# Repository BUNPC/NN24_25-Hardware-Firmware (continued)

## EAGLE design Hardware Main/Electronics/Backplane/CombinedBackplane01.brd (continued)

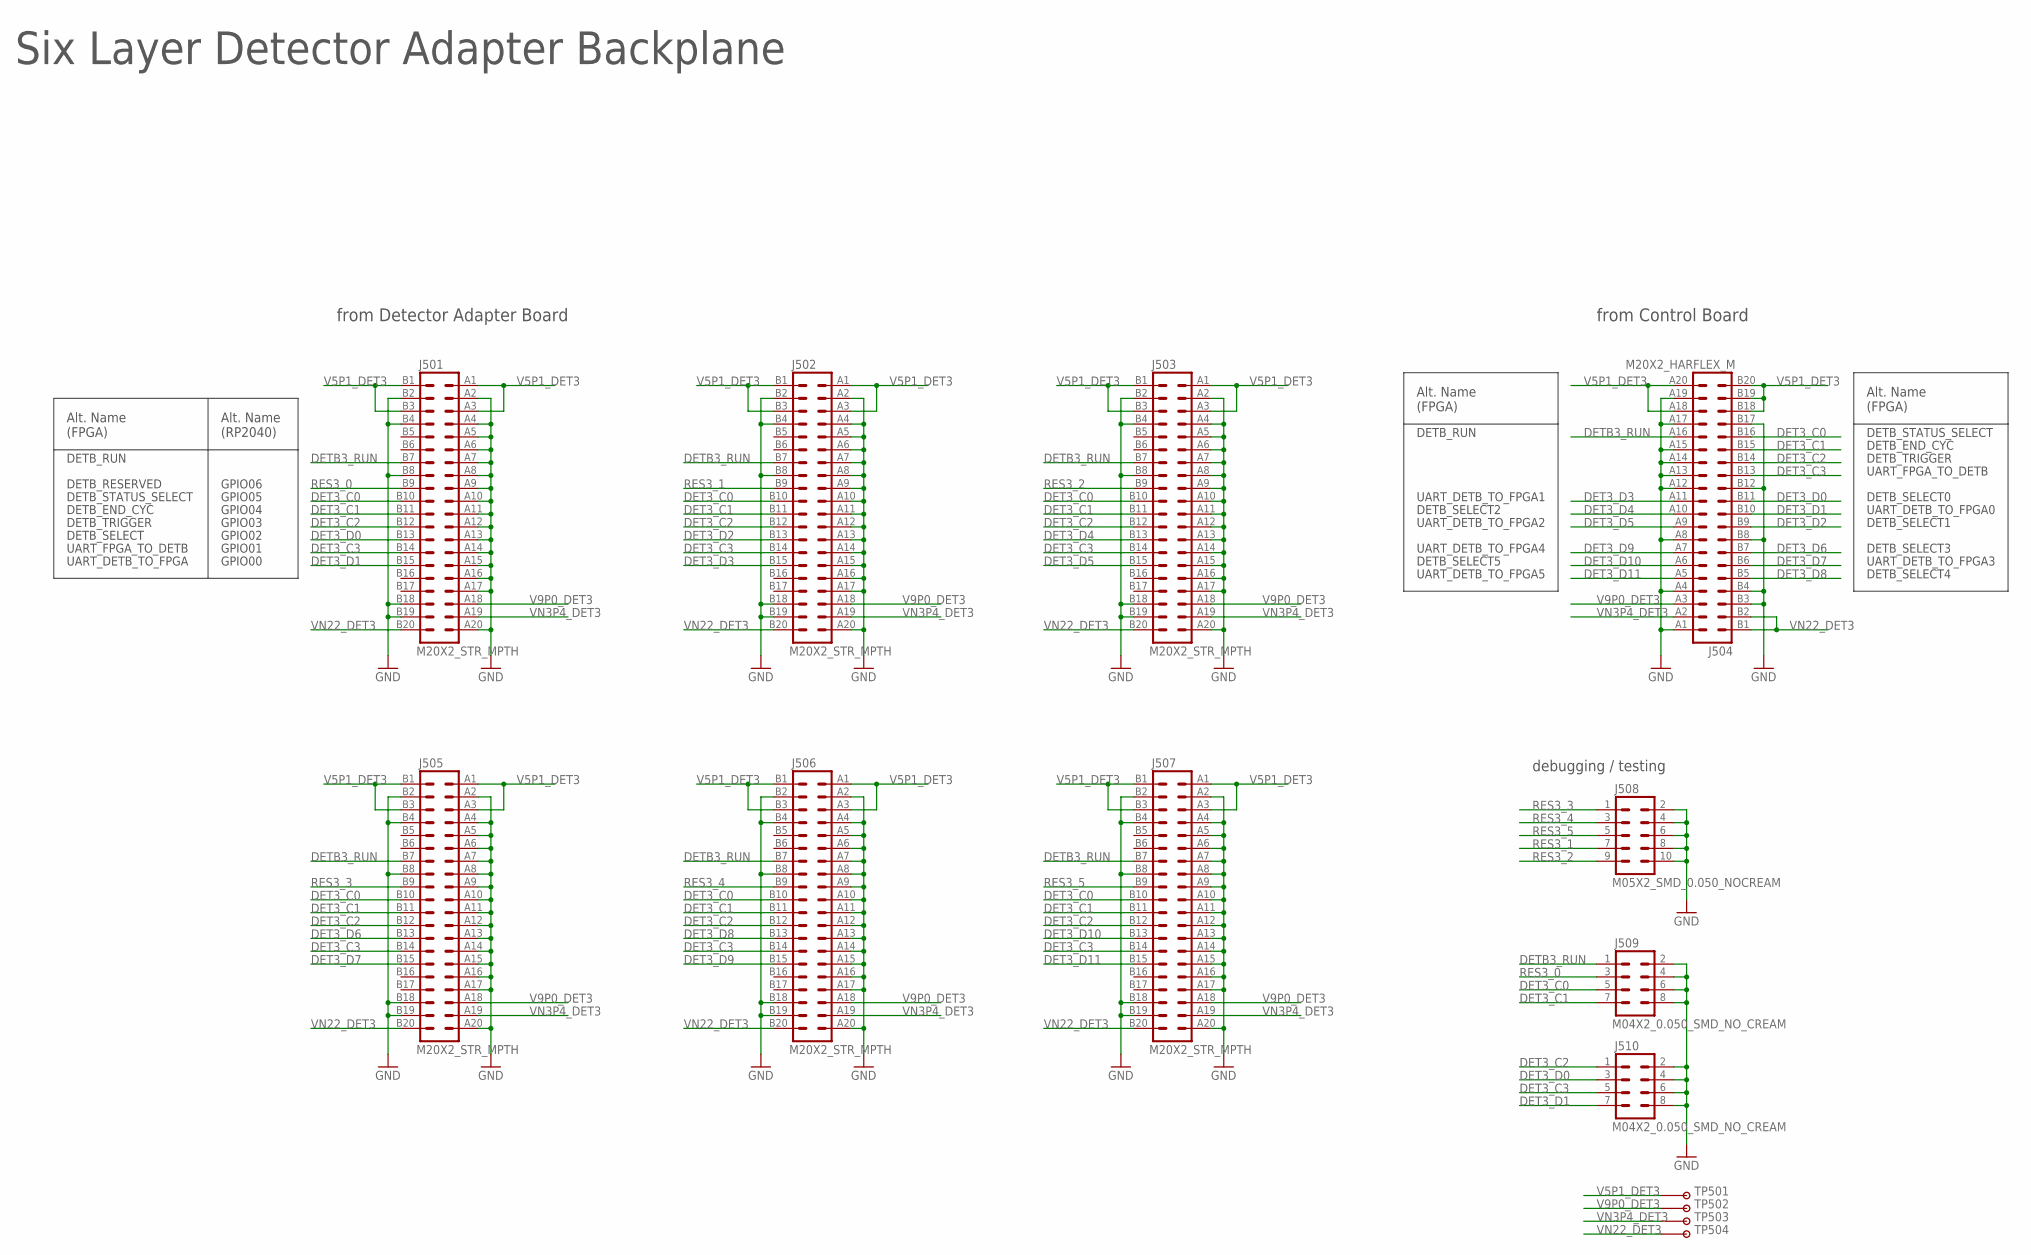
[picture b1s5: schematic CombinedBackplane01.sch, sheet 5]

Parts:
J501, J502, J503, J505, J506, J507: M20X2_STR_MPTH; M20X2_HARFLEX_F_STR_MPTH
J504: M20X2_HARFLEX_M
J508: M05X2_SMD_0.050_NOCREAM; M05X2_0.050_SMD_NO_CREAM
J509, J510: M04X2_0.050_SMD_NO_CREAM
TP501, TP502, TP503, TP504: TESTPOINT_ROUND; TESTPAD_ROUND

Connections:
DET3_C0: J501.B10 (19), J502.B10 (19), J503.B10 (19), J504.B16 (31), J505.B10 (19), J506.B10 (19), J507.B10 (19), J509.5
DET3_C1: J501.B11 (21), J502.B11 (21), J503.B11 (21), J504.B15 (29), J505.B11 (21), J506.B11 (21), J507.B11 (21), J509.7
DET3_C2: J501.B12 (23), J502.B12 (23), J503.B12 (23), J504.B14 (27), J505.B12 (23), J506.B12 (23), J507.B12 (23), J510.1
DET3_C3: J501.B14 (27), J502.B14 (27), J503.B14 (27), J504.B13 (25), J505.B14 (27), J506.B14 (27), J507.B14 (27), J510.5
DET3_D0: J501.B13 (25), J504.B11 (21), J510.3
DET3_D1: J501.B15 (29), J504.B10 (19), J510.7
DET3_D2: J502.B13 (25), J504.B9 (17)
DET3_D3: J502.B15 (29), J504.A11 (22)
DET3_D4: J503.B13 (25), J504.A10 (20)
DET3_D5: J503.B15 (29), J504.A9 (18)
DET3_D6: J504.B7 (13), J505.B13 (25)
DET3_D7: J504.B6 (11), J505.B15 (29)
DET3_D8: J504.B5 (9), J506.B13 (25)
DET3_D9: J504.A7 (14), J506.B15 (29)
DET3_D10: J504.A6 (12), J507.B13 (25)
DET3_D11: J504.A5 (10), J507.B15 (29)
DETB3_RUN: J501.B7 (13), J502.B7 (13), J503.B7 (13), J504.A16 (32), J505.B7 (13), J506.B7 (13), J507.B7 (13), J509.1
GND: J501.A2 (4), J501.A4 (8), J501.A5 (10), J501.A6 (12), J501.A7 (14), J501.A8 (16), J501.A9 (18), J501.A10 (20), J501.A11 (22), J501.A12 (24), J501.A13 (26), J501.A14 (28), J501.A15 (30), J501.A16 (32), J501.A17 (34), J501.A20 (40), J501.B2 (3), J501.B4 (7), J501.B8 (15), J501.B18 (35), J501.B19 (37), J502.A2 (4), J502.A4 (8), J502.A5 (10), J502.A6 (12), J502.A7 (14), J502.A8 (16), J502.A9 (18), J502.A10 (20), J502.A11 (22), J502.A12 (24), J502.A13 (26), J502.A14 (28), J502.A15 (30), J502.A16 (32), J502.A17 (34), J502.A20 (40), J502.B2 (3), J502.B4 (7), J502.B8 (15), J502.B18 (35), J502.B19 (37), J503.A2 (4), J503.A4 (8), J503.A5 (10), J503.A6 (12), J503.A7 (14), J503.A8 (16), J503.A9 (18), J503.A10 (20), J503.A11 (22), J503.A12 (24), J503.A13 (26), J503.A14 (28), J503.A15 (30), J503.A16 (32), J503.A17 (34), J503.A20 (40), J503.B2 (3), J503.B4 (7), J503.B8 (15), J503.B18 (35), J503.B19 (37), J504.A1 (2), J504.A4 (8), J504.A8 (16), J504.A12 (24), J504.A13 (26), J504.A14 (28), J504.A15 (30), J504.A17 (34), J504.A19 (38), J504.B3 (5), J504.B4 (7), J504.B8 (15), J504.B12 (23), J504.B17 (33), J505.A2 (4), J505.A4 (8), J505.A5 (10), J505.A6 (12), J505.A7 (14), J505.A8 (16), J505.A9 (18), J505.A10 (20), J505.A11 (22), J505.A12 (24), J505.A13 (26), J505.A14 (28), J505.A15 (30), J505.A16 (32), J505.A17 (34), J505.A20 (40), J505.B2 (3), J505.B4 (7), J505.B8 (15), J505.B18 (35), J505.B19 (37), J506.A2 (4), J506.A4 (8), J506.A5 (10), J506.A6 (12), J506.A7 (14), J506.A8 (16), J506.A9 (18), J506.A10 (20), J506.A11 (22), J506.A12 (24), J506.A13 (26), J506.A14 (28), J506.A15 (30), J506.A16 (32), J506.A17 (34), J506.A20 (40), J506.B2 (3), J506.B4 (7), J506.B8 (15), J506.B18 (35), J506.B19 (37), J507.A2 (4), J507.A4 (8), J507.A5 (10), J507.A6 (12), J507.A7 (14), J507.A8 (16), J507.A9 (18), J507.A10 (20), J507.A11 (22), J507.A12 (24), J507.A13 (26), J507.A14 (28), J507.A15 (30), J507.A16 (32), J507.A17 (34), J507.A20 (40), J507.B2 (3), J507.B4 (7), J507.B8 (15), J507.B18 (35), J507.B19 (37), J508.2, J508.4, J508.6, J508.8, J508.10, J509.2, J509.4, J509.6, J509.8, J510.2, J510.4, J510.6, J510.8; also elsewhere on the board
RES3_0: J501.B9 (17), J509.3
RES3_1: J502.B9 (17), J508.7
RES3_2: J503.B9 (17), J508.9
RES3_3: J505.B9 (17), J508.1
RES3_4: J506.B9 (17), J508.3
RES3_5: J507.B9 (17), J508.5
V5P1_DET3: J501.A1 (2), J501.A3 (6), J501.B1 (1), J501.B3 (5), J502.A1 (2), J502.A3 (6), J502.B1 (1), J502.B3 (5), J503.A1 (2), J503.A3 (6), J503.B1 (1), J503.B3 (5), J504.A18 (36), J504.A20 (40), J504.B18 (35), J504.B19 (37), J504.B20 (39), J505.A1 (2), J505.A3 (6), J505.B1 (1), J505.B3 (5), J506.A1 (2), J506.A3 (6), J506.B1 (1), J506.B3 (5), J507.A1 (2), J507.A3 (6), J507.B1 (1), J507.B3 (5), TP501.P$1
V9P0_DET3: J501.A18 (36), J502.A18 (36), J503.A18 (36), J504.A3 (6), J505.A18 (36), J506.A18 (36), J507.A18 (36), TP502.P$1
VN3P4_DET3: J501.A19 (38), J502.A19 (38), J503.A19 (38), J504.A2 (4), J505.A19 (38), J506.A19 (38), J507.A19 (38), TP503.P$1
VN22_DET3: J501.B20 (39), J502.B20 (39), J503.B20 (39), J504.B1 (1), J504.B2 (3), J505.B20 (39), J506.B20 (39), J507.B20 (39), TP504.P$1

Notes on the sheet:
Six Layer Detector Adapter Backplane
from Detector Adapter Board
from Control Board
GPIO00
GPIO01
GPIO02
GPIO03
GPIO04
GPIO05
GPIO06
UART_DETB_TO_FPGA
UART_FPGA_TO_DETB
DETB_SELECT
DETB_TRIGGER
DETB_END_CYC
DETB_STATUS_SELECT
DETB_RESERVED
DETB_RUN
debugging / testing
UART_DETB_TO_FPGA0
DETB_SELECT0
DETB_SELECT1
DETB_SELECT2
DETB_SELECT5
DETB_SELECT3
DETB_SELECT4
UART_DETB_TO_FPGA1
UART_DETB_TO_FPGA2
UART_DETB_TO_FPGA4
UART_DETB_TO_FPGA5
UART_DETB_TO_FPGA3
Alt. Name (FPGA)
Alt. Name (RP2040)

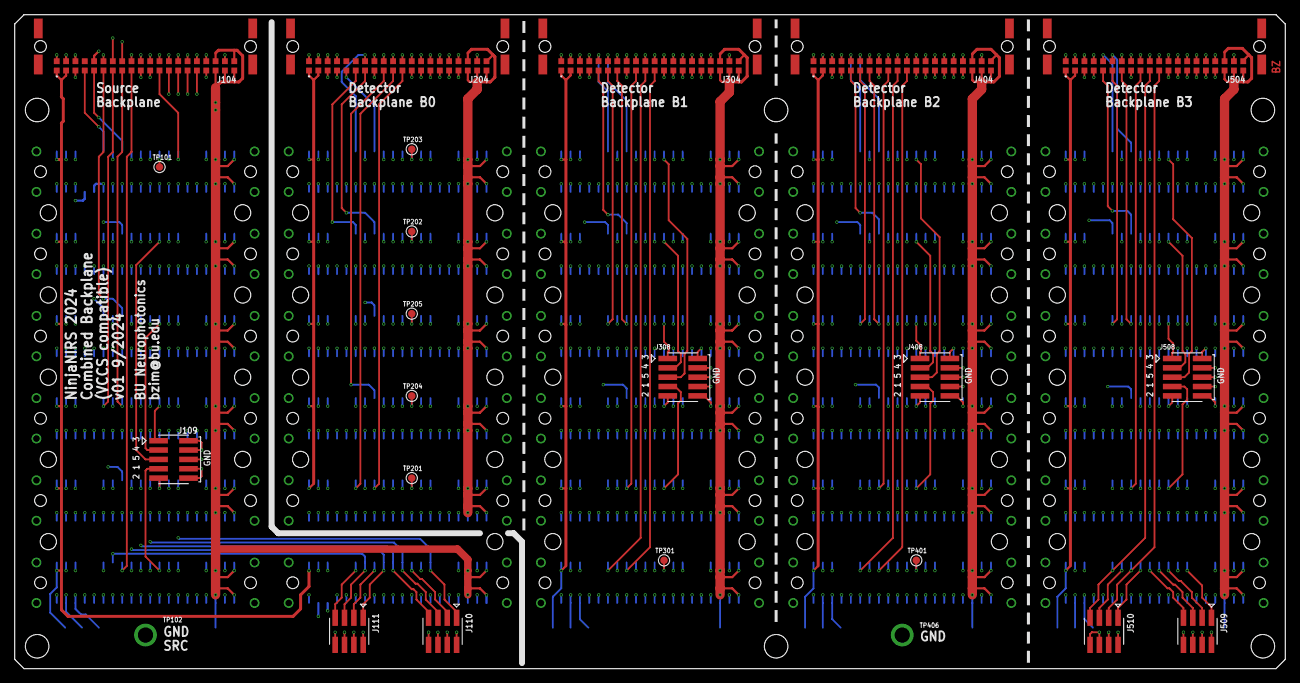
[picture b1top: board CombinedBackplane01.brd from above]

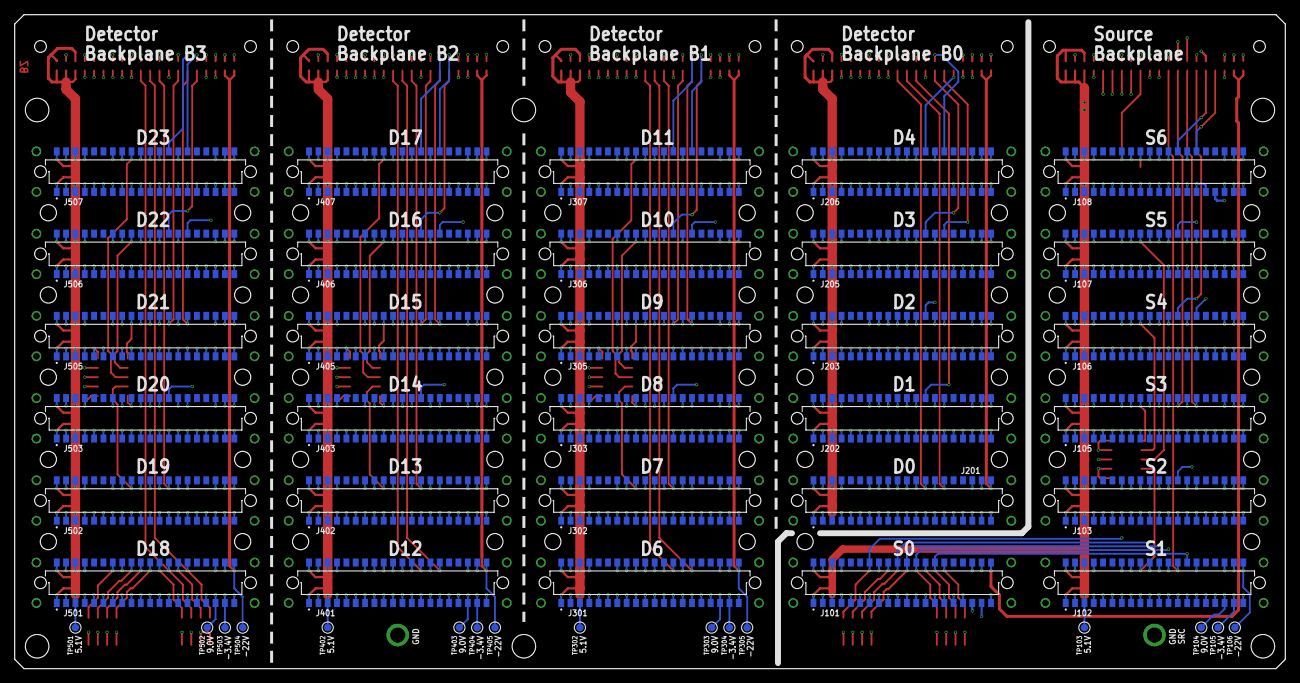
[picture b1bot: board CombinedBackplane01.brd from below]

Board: 4 copper layers, 172.7 x 88.9 mm, 69 parts (46 on the bottom side), 137 nets.

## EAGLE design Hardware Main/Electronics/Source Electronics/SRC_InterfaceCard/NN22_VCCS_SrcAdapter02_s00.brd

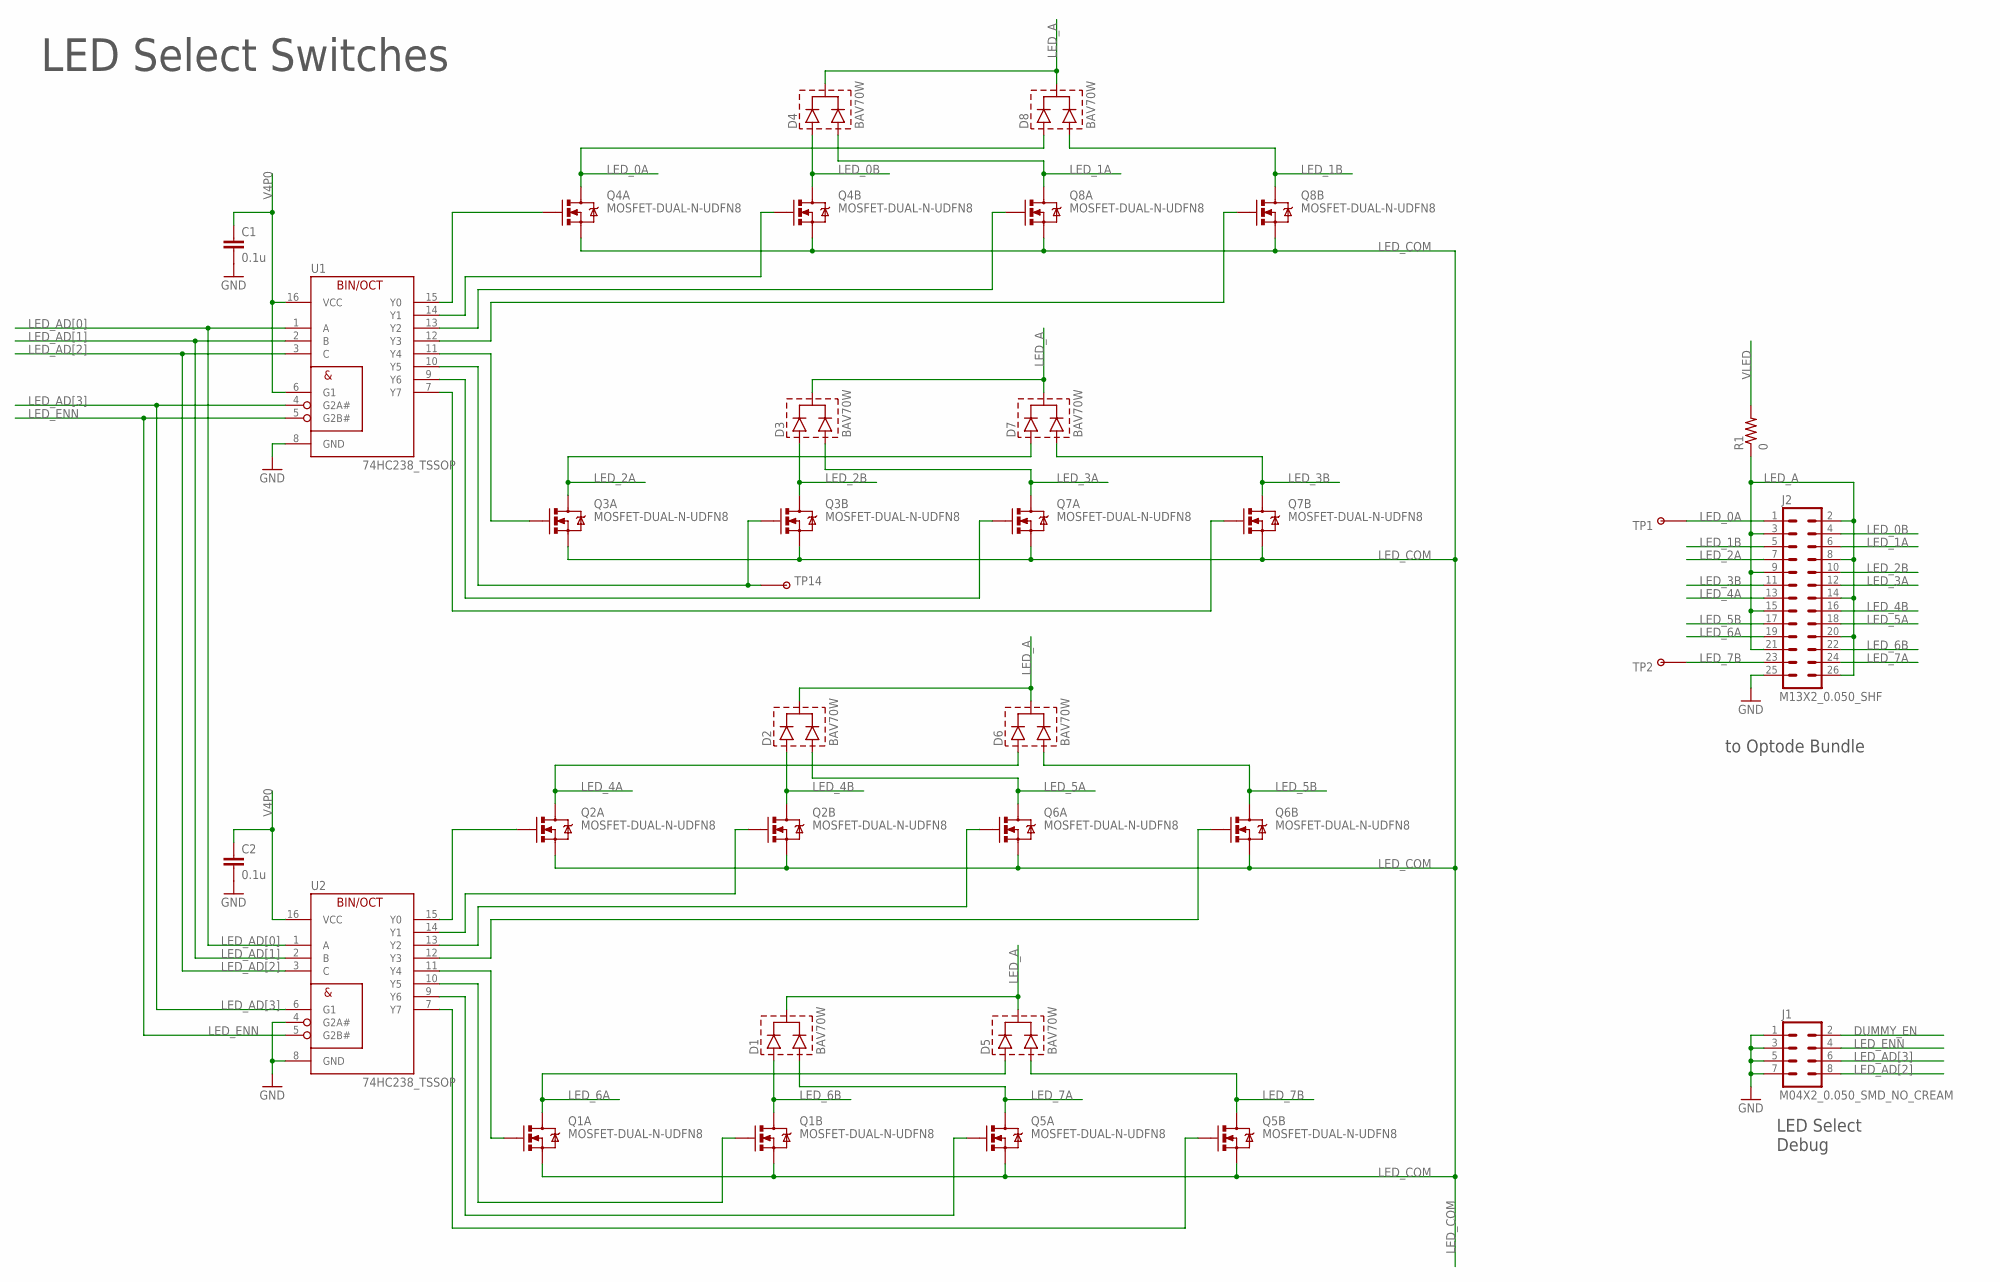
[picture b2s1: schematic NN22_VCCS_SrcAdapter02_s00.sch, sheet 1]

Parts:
C1, C2: 0.1u; 0402-CAP
D1, D2, D3, D4, D5, D6, D7, D8: BAV70W; SOT323
J1: M04X2_0.050_SMD_NO_CREAM
J2: M13X2_0.050_SHF
Q1, Q2, Q3, Q4, Q5, Q6, Q7, Q8: MOSFET-DUAL-N-UDFN8; UDFN8
R1: 0; 1206
TP1, TP2: TESTPOINT_ROUND; TESTPAD_ROUND
TP14: TESTPOINTPADSMALL; TESTPAD_SMALL
U1, U2: 74HC238_TSSOP; TSSOP16

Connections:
DUMMY_EN: J1.2; also elsewhere on the board
GND: C1.2, C2.2, J1.1, J1.3, J1.5, J1.7, J2.25, U1.8 (GND), U2.4 (G2A#), U2.8 (GND); also elsewhere on the board
LED_0A: D8.1 (A1), J2.1, Q4.6 (D), Q4.P1 (D), TP1.P$1
LED_0B: D4.1 (A1), J2.4, Q4.3 (D), Q4.P2 (D)
LED_1A: D4.2 (A2), J2.6, Q8.6 (D), Q8.P1 (D)
LED_1B: D8.2 (A2), J2.5, Q8.3 (D), Q8.P2 (D)
LED_2A: D7.1 (A1), J2.7, Q3.6 (D), Q3.P1 (D)
LED_2B: D3.1 (A1), J2.10, Q3.3 (D), Q3.P2 (D)
LED_3A: D3.2 (A2), J2.12, Q7.6 (D), Q7.P1 (D)
LED_3B: D7.2 (A2), J2.11, Q7.3 (D), Q7.P2 (D)
LED_4A: D6.1 (A1), J2.13, Q2.6 (D), Q2.P1 (D)
LED_4B: D2.1 (A1), J2.16, Q2.3 (D), Q2.P2 (D)
LED_5A: D2.2 (A2), J2.18, Q6.6 (D), Q6.P1 (D)
LED_5B: D6.2 (A2), J2.17, Q6.3 (D), Q6.P2 (D)
LED_6A: D5.1 (A1), J2.19, Q1.6 (D), Q1.P1 (D)
LED_6B: D1.1 (A1), J2.22, Q1.3 (D), Q1.P2 (D)
LED_7A: D1.2 (A2), J2.24, Q5.6 (D), Q5.P1 (D)
LED_7B: D5.2 (A2), J2.23, Q5.3 (D), Q5.P2 (D), TP2.P$1
LED_A: D1.3 (C), D2.3 (C), D3.3 (C), D4.3 (C), D5.3 (C), D6.3 (C), D7.3 (C), D8.3 (C), J2.2, J2.3, J2.8, J2.9, J2.14, J2.15, J2.20, J2.21, J2.26, R1.1
LED_AD[0]: U1.1 (A), U2.1 (A); also elsewhere on the board
LED_AD[1]: U1.2 (B), U2.2 (B); also elsewhere on the board
LED_AD[2]: J1.8, U1.3 (C), U2.3 (C); also elsewhere on the board
LED_AD[3]: J1.6, U1.4 (G2A#), U2.6 (G1); also elsewhere on the board
LED_COM: Q1.1 (S), Q1.4 (S), Q2.1 (S), Q2.4 (S), Q3.1 (S), Q3.4 (S), Q4.1 (S), Q4.4 (S), Q5.1 (S), Q5.4 (S), Q6.1 (S), Q6.4 (S), Q7.1 (S), Q7.4 (S), Q8.1 (S), Q8.4 (S); also elsewhere on the board
LED_ENN: J1.4, U1.5 (G2B#), U2.5 (G2B#); also elsewhere on the board
unnamed: Q4.5 (G), U1.14 (Y1)
unnamed: Q3.5 (G), TP14.P$1, U1.10 (Y5)
unnamed: Q8.5 (G), U1.12 (Y3)
unnamed: Q8.2 (G), U1.13 (Y2)
unnamed: Q7.5 (G), U1.7 (Y7)
unnamed: Q7.2 (G), U1.9 (Y6)
unnamed: Q2.5 (G), U2.14 (Y1)
unnamed: Q6.5 (G), U2.12 (Y3)
unnamed: Q6.2 (G), U2.13 (Y2)
unnamed: Q1.5 (G), U2.10 (Y5)
unnamed: Q5.5 (G), U2.7 (Y7)
unnamed: Q5.2 (G), U2.9 (Y6)
unnamed: Q4.2 (G), U1.15 (Y0)
unnamed: Q3.2 (G), U1.11 (Y4)
unnamed: Q2.2 (G), U2.15 (Y0)
unnamed: Q1.2 (G), U2.11 (Y4)
V4P0: C1.1, C2.1, U1.6 (G1), U1.16 (VCC), U2.16 (VCC); also elsewhere on the board
VLED: R1.2; also elsewhere on the board

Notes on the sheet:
to Optode Bundle
LED Select Switches
LED Select Debug

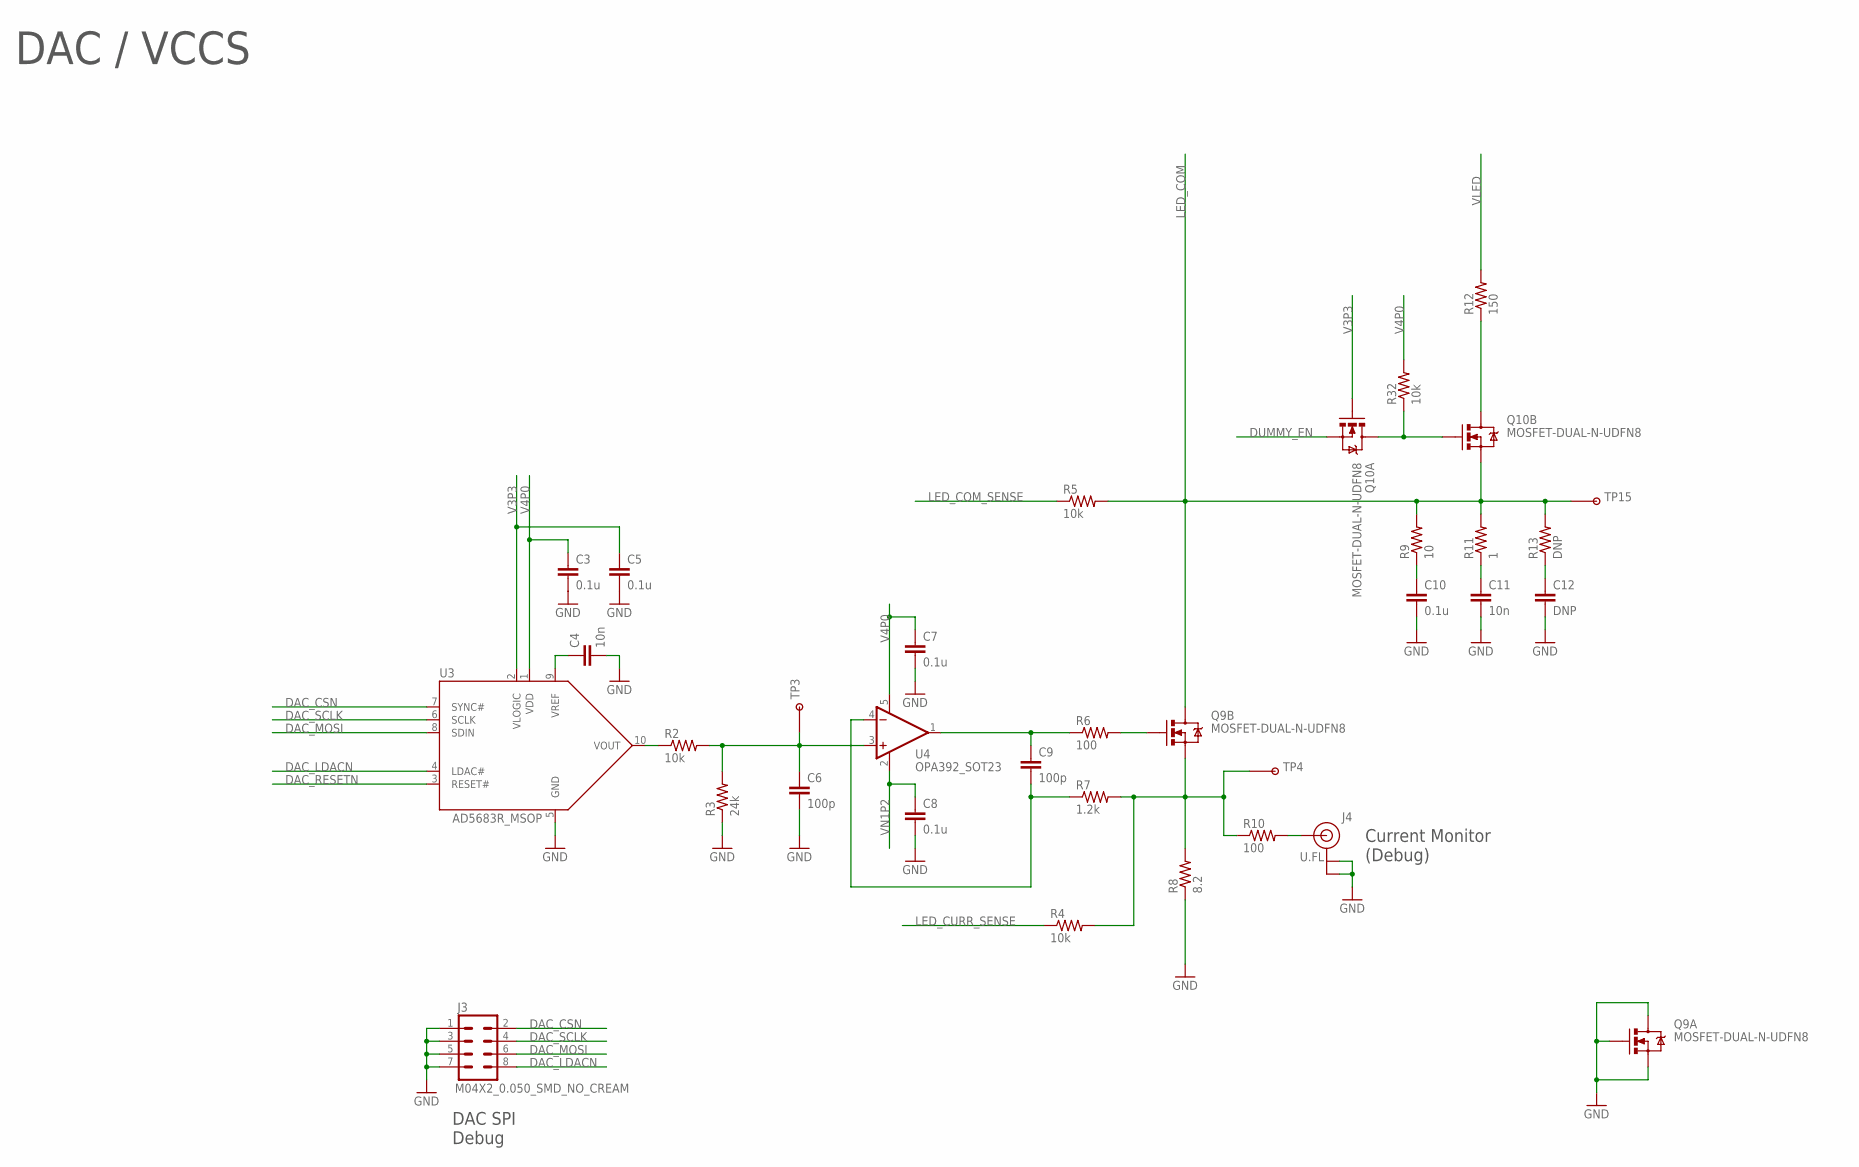
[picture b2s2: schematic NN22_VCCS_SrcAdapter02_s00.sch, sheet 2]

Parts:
C3, C5, C7, C8, C10: 0.1u; 0402-CAP
C4, C11: 10n; 0402-CAP
C6, C9: 100p; 0402-CAP
C12: DNP; 0603-CAP
J3: M04X2_0.050_SMD_NO_CREAM
J4: U.FL
Q9, Q10: MOSFET-DUAL-N-UDFN8; UDFN8
R2, R4, R5, R32: 10k; 0402-RES
R3: 24k; 0402-RES
R6, R10: 100; 0402-RES
R7: 1.2k; 0402-RES
R8: 8.2; R2512
R9: 10; 0603-RES
R11: 1; 0603-RES
R12: 150; 0603-RES
R13: DNP; 0603-RES
TP3, TP4, TP15: TESTPOINT_ROUND; TESTPAD_ROUND
U3: AD5683R_MSOP; MSOP10
U4: OPA392_SOT23; SOT23-5

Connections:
DAC_CSN: J3.2, U3.7 (SYNC#); also elsewhere on the board
DAC_LDACN: J3.8, U3.4 (LDAC#); also elsewhere on the board
DAC_MOSI: J3.6, U3.8 (SDIN); also elsewhere on the board
DAC_RESETN: U3.3 (RESET#); also elsewhere on the board
DAC_SCLK: J3.4, U3.6 (SCLK); also elsewhere on the board
DUMMY_EN: Q10.1 (S); also elsewhere on the board
GND: C3.2, C4.2, C5.2, C6.2, C7.2, C8.2, C10.2, C11.2, C12.2, J3.1, J3.3, J3.5, J3.7, J4.P$1 (GND), J4.P$2 (GND), Q9.1 (S), Q9.2 (G), Q9.6 (D), Q9.P1 (D), R3.1, R8.1, U3.5 (GND); also elsewhere on the board
LED_COM: Q9.3 (D), Q9.P2 (D), Q10.4 (S), R5.2, R9.2, R11.2, R13.2, TP15.P$1; also elsewhere on the board
LED_COM_SENSE: R5.1; also elsewhere on the board
LED_CURR_SENSE: R4.1; also elsewhere on the board
unnamed: Q9.5 (G), R6.2
unnamed: R2.1, U3.10 (VOUT)
unnamed: Q10.3 (D), Q10.P2 (D), R12.1
unnamed: C6.1, R2.2, R3.2, TP3.P$1, U4.3 (+IN)
unnamed: C9.1, R6.1, U4.1 (OUT)
unnamed: Q10.5 (G), Q10.6 (D), Q10.P1 (D), R32.1
unnamed: Q9.4 (S), R4.2, R7.2, R8.2, R10.1, TP4.P$1
unnamed: C9.2, R7.1, U4.4 (-IN)
unnamed: C4.1, U3.9 (VREF)
unnamed: J4.P$3 (SIGNAL), R10.2
unnamed: C11.1, R11.1
unnamed: C10.1, R9.1
unnamed: C12.1, R13.1
V3P3: C5.1, Q10.2 (G), U3.2 (VLOGIC); also elsewhere on the board
V4P0: C3.1, C7.1, R32.2, U3.1 (VDD), U4.5 (V+); also elsewhere on the board
VLED: R12.2; also elsewhere on the board
VN1P2: C8.1, U4.2 (V-); also elsewhere on the board

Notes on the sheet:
DAC SPI Debug
DAC / VCCS
Current Monitor (Debug)

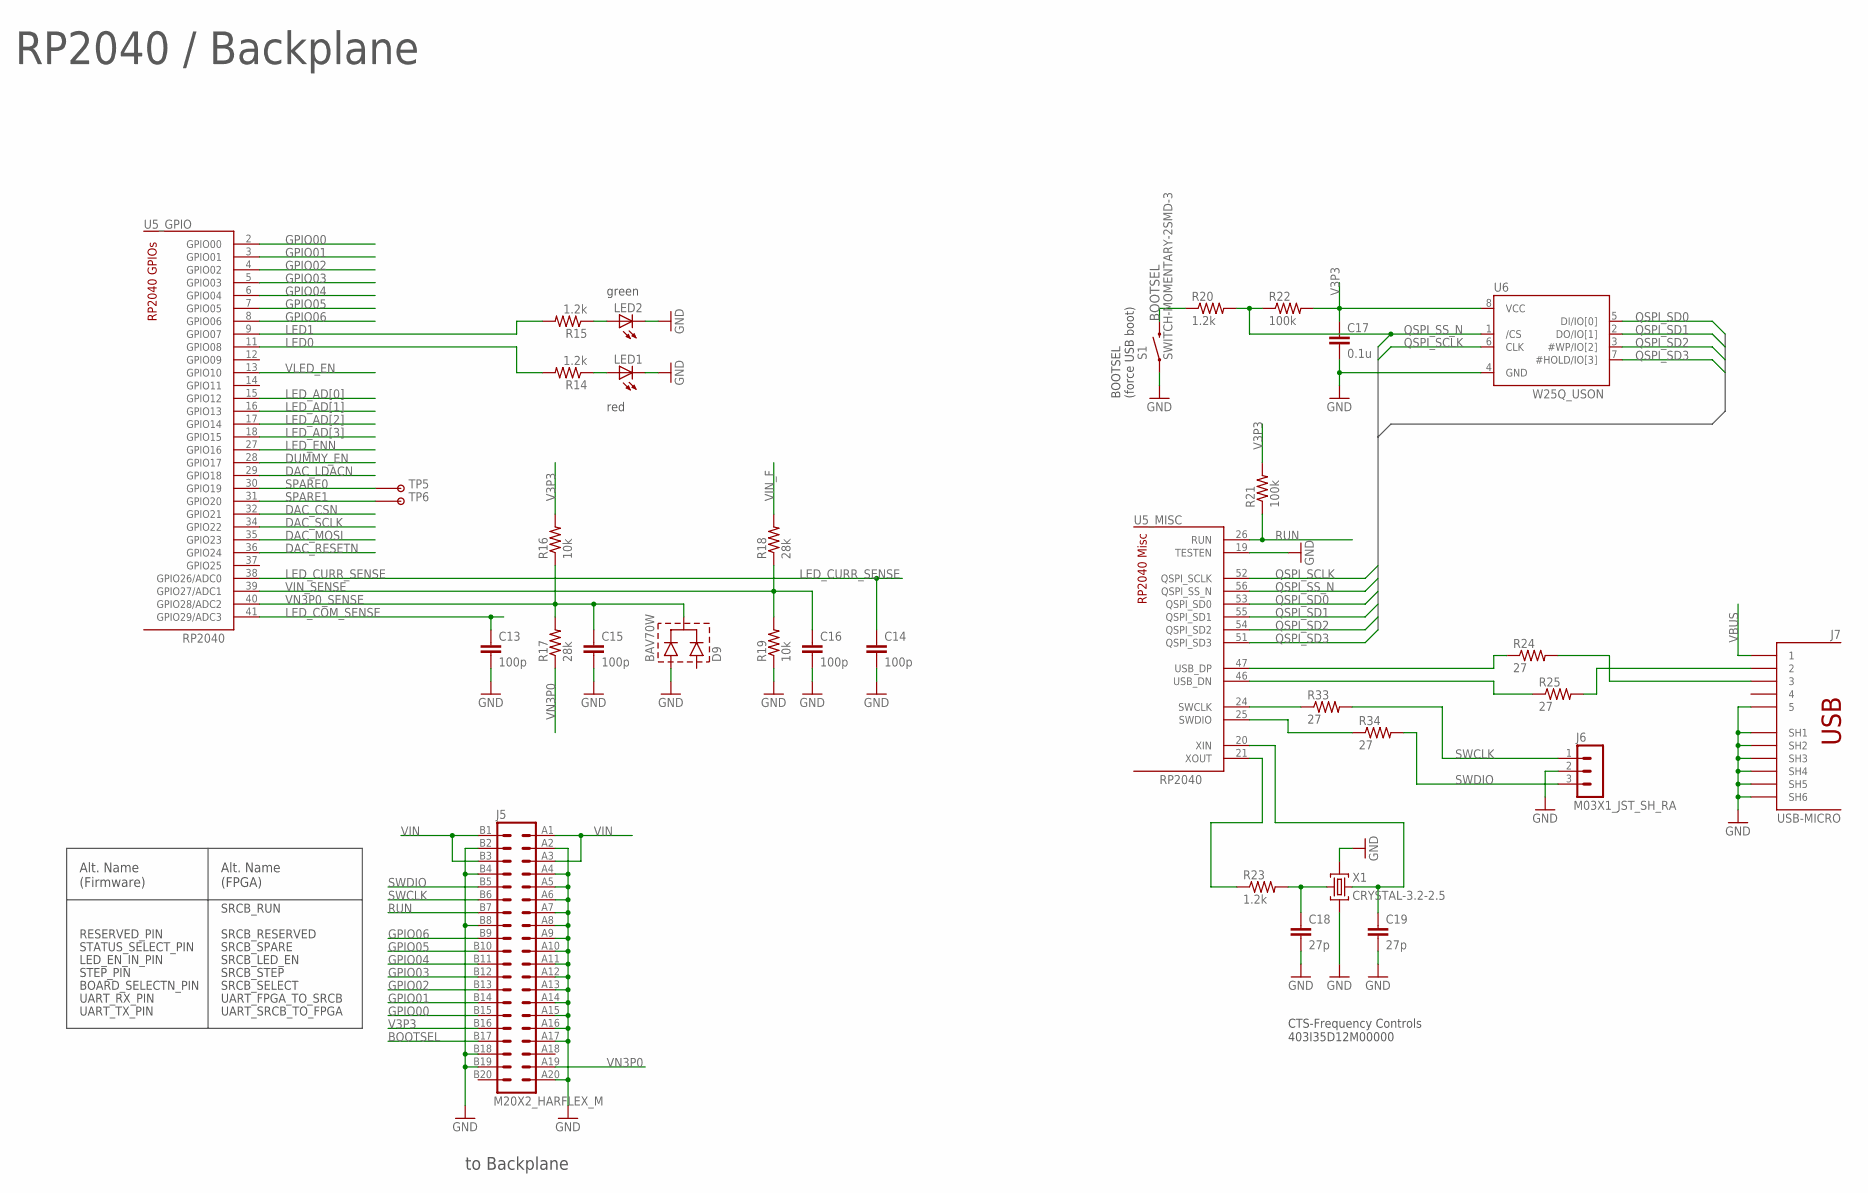
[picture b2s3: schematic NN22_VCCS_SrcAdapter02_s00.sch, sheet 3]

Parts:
C13, C14, C15, C16: 100p; 0402-CAP
C17: 0.1u; 0402-CAP
C18, C19: 27p; 0402-CAP
D9: BAV70W; SOT323
J5: M20X2_HARFLEX_M
J6: M03X1_JST_SH_RA; M03X1_JST_SH_SM_RA
J7: USB-MICRO
LED1, LED2: LED0603; LED-0603
R14, R15, R20, R23: 1.2k; 0402-RES
R16, R19: 10k; 0402-RES
R17, R18: 28k; 0402-RES
R21, R22: 100k; 0402-RES
R24, R25, R33, R34: 27; 0402-RES
S1: SWITCH-MOMENTARY-2SMD-3; TACTILE_SWITCH_SMD-3
TP5, TP6: TESTPOINTPADSMALL; TESTPAD_SMALL
U5: RP2040; QFN-56_EP
U6: W25Q_USON; USON8L-2X3MM
X1: CRYSTAL-3.2-2.5

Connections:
BOOTSEL: J5.B17 (33), R20.1, S1.4 (2)
DAC_CSN: U5.32 (GPIO21); also elsewhere on the board
DAC_LDACN: U5.29 (GPIO18); also elsewhere on the board
DAC_MOSI: U5.35 (GPIO23); also elsewhere on the board
DAC_RESETN: U5.36 (GPIO24); also elsewhere on the board
DAC_SCLK: U5.34 (GPIO22); also elsewhere on the board
DUMMY_EN: U5.28 (GPIO17); also elsewhere on the board
GND: C13.2, C14.2, C15.2, C16.2, C17.2, C18.2, C19.2, D9.2 (A2), J5.A2 (4), J5.A4 (8), J5.A5 (10), J5.A6 (12), J5.A7 (14), J5.A8 (16), J5.A9 (18), J5.A10 (20), J5.A11 (22), J5.A12 (24), J5.A13 (26), J5.A14 (28), J5.A15 (30), J5.A16 (32), J5.A17 (34), J5.A20 (40), J5.B2 (3), J5.B4 (7), J5.B8 (15), J5.B18 (35), J5.B19 (37), J6.2, J7.5, J7.SH1, J7.SH2, J7.SH3, J7.SH4, J7.SH5, J7.SH6, LED1.C, LED2.C, R19.1, S1.1, U5.19 (TESTEN), U6.4 (GND), X1.2 (GND), X1.4 (GND); also elsewhere on the board
GPIO00: J5.B15 (29), U5.2 (GPIO00)
GPIO01: J5.B14 (27), U5.3 (GPIO01)
GPIO02: J5.B13 (25), U5.4 (GPIO02)
GPIO03: J5.B12 (23), U5.5 (GPIO03)
GPIO04: J5.B11 (21), U5.6 (GPIO04)
GPIO05: J5.B10 (19), U5.7 (GPIO05)
GPIO06: J5.B9 (17), U5.8 (GPIO06)
LED0: R14.2, U5.11 (GPIO08)
LED1: R15.2, U5.9 (GPIO07)
LED_AD[0]: U5.15 (GPIO12); also elsewhere on the board
LED_AD[1]: U5.16 (GPIO13); also elsewhere on the board
LED_AD[2]: U5.17 (GPIO14); also elsewhere on the board
LED_AD[3]: U5.18 (GPIO15); also elsewhere on the board
LED_COM_SENSE: C13.1, U5.41 (GPIO29/ADC3); also elsewhere on the board
LED_CURR_SENSE: C14.1, U5.38 (GPIO26/ADC0); also elsewhere on the board
LED_ENN: U5.27 (GPIO16); also elsewhere on the board
unnamed: C19.1, U5.20 (XIN), X1.3 (C2)
unnamed: C18.1, R23.2, X1.1 (C1)
unnamed: R23.1, U5.21 (XOUT)
unnamed: R24.1, U5.47 (USB_DP)
unnamed: R25.1, U5.46 (USB_DN)
unnamed: R34.1, U5.25 (SWDIO)
unnamed: R33.1, U5.24 (SWCLK)
unnamed: J7.2, R25.2
unnamed: J7.3, R24.2
unnamed: LED1.A, R14.1
unnamed: LED2.A, R15.1
QSPI_SCLK: U5.52 (QSPI_SCLK), U6.6 (CLK)
QSPI_SD0: U5.53 (QSPI_SD0), U6.5 (DI/IO[0])
QSPI_SD1: U5.55 (QSPI_SD1), U6.2 (DO/IO[1])
QSPI_SD2: U5.54 (QSPI_SD2), U6.3 (#WP/IO[2])
QSPI_SD3: U5.51 (QSPI_SD3), U6.7 (#HOLD/IO[3])
QSPI_SS_N: R20.2, R22.1, U5.56 (QSPI_SS_N), U6.1 (/CS)
RUN: J5.B7 (13), R21.1, U5.26 (RUN)
SPARE0: TP5.P$1, U5.30 (GPIO19)
SPARE1: TP6.P$1, U5.31 (GPIO20)
SWCLK: J5.B6 (11), J6.1, R33.2
SWDIO: J5.B5 (9), J6.3, R34.2
V3P3: C17.1, J5.B16 (31), R16.2, R21.2, R22.2, U6.8 (VCC); also elsewhere on the board
VBUS: J7.1; also elsewhere on the board
VIN: J5.A1 (2), J5.A3 (6), J5.B1 (1), J5.B3 (5); also elsewhere on the board
VIN_F: R18.2; also elsewhere on the board
VIN_SENSE: C16.1, R18.1, R19.2, U5.39 (GPIO27/ADC1)
VLED_EN: U5.13 (GPIO10); also elsewhere on the board
VN3P0: J5.A19 (38), R17.1; also elsewhere on the board
VN3P0_SENSE: C15.1, D9.3 (C), R16.1, R17.2, U5.40 (GPIO28/ADC2)

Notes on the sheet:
BOOTSEL (force USB boot)
RP2040 / Backplane
to Backplane
CTS-Frequency Controls 403I35D12M00000
UART_SRCB_TO_FPGA
UART_FPGA_TO_SRCB
SRCB_SELECT
SRCB_STEP
SRCB_LED_EN
SRCB_SPARE
SRCB_RESERVED
SRCB_RUN
Alt. Name (FPGA)
red
green
Alt. Name (Firmware)
UART_TX_PIN
UART_RX_PIN
BOARD_SELECTN_PIN
STEP_PIN
LED_EN_IN_PIN
STATUS_SELECT_PIN
RESERVED_PIN

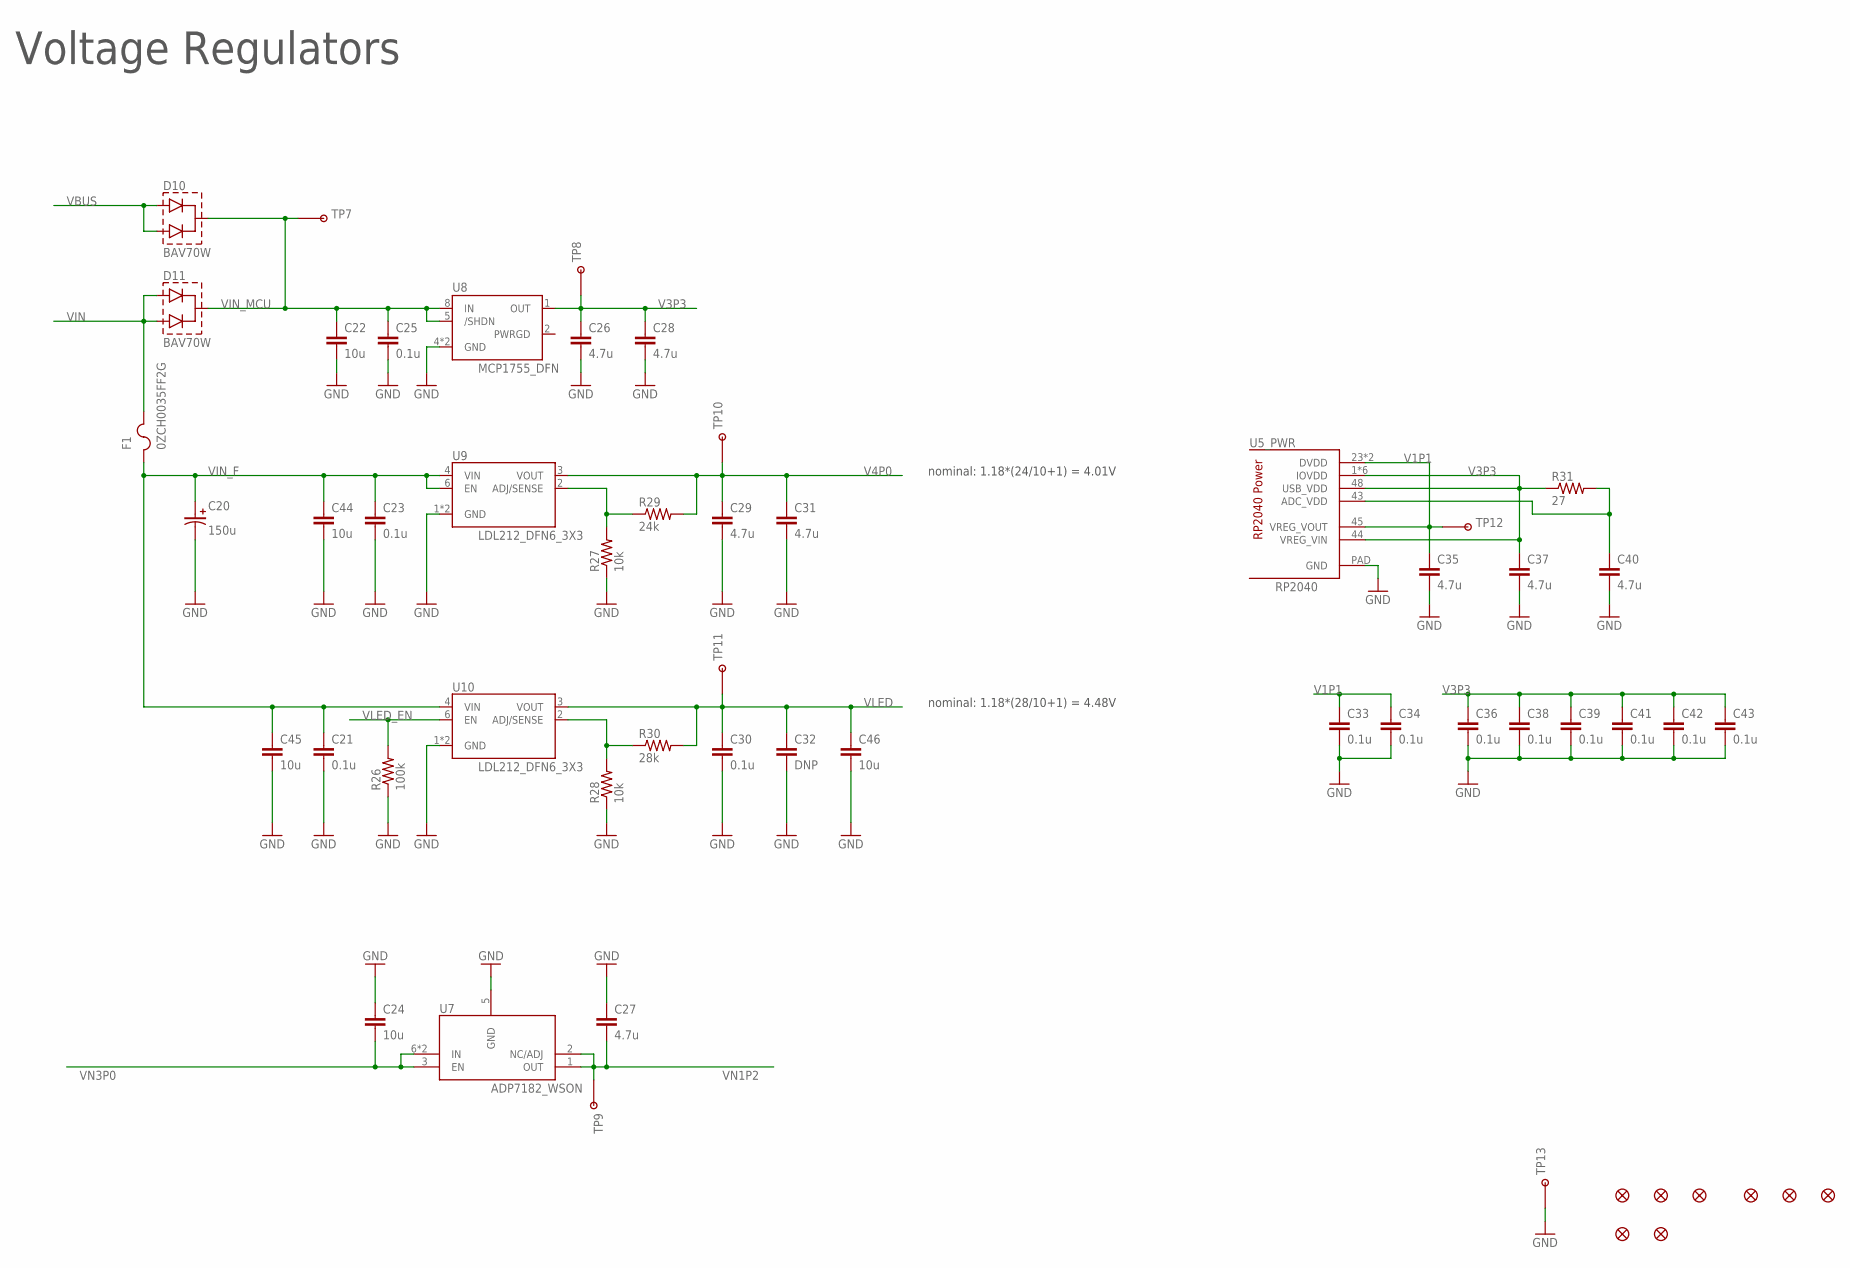
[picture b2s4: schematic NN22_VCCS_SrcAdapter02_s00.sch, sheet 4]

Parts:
C20: 150u; 2917-CAP
C21, C23, C25, C30, C33, C34, C36, C38, C39, C41, C42, C43: 0.1u; 0402-CAP
C22, C24, C44, C45, C46: 10u; 0603-CAP
C26, C27, C28, C29, C31, C35, C37, C40: 4.7u; 0402-CAP
C32: DNP; 0402-CAP
D10, D11: BAV70W; SOT323
F1: 0ZCH0035FF2G; 1210-FUSE
FID1, FID2, FID3, FID4, FID5, FID6, FID7, FID8: FIDUCIALUFIDUCIAL; MICRO-FIDUCIAL
R26: 100k; 0402-RES
R27, R28: 10k; 0402-RES
R29: 24k; 0402-RES
R30: 28k; 0402-RES
R31: 27; 0402-RES
TP7, TP8, TP9, TP10, TP11: TESTPOINT_ROUND; TESTPAD_ROUND
TP12: TESTPOINTPADSMALL; TESTPAD_SMALL
TP13: TESTPOINT1X01; 1X01
U5: RP2040; QFN-56_EP
U7: ADP7182_WSON; WSON6
U8: MCP1755_DFN; DFN8_2X3MM
U9, U10: LDL212_DFN6_3X3; DFN6_3X3MM

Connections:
GND: C20.N, C21.2, C22.2, C23.2, C24.1, C25.2, C26.2, C27.1, C28.2, C29.2, C30.2, C31.2, C32.2, C33.2, C34.2, C35.2, C36.2, C37.2, C38.2, C39.2, C40.2, C41.2, C42.2, C43.2, C44.2, C45.2, C46.2, R26.1, R27.1, R28.1, TP13.1, U5.PAD (GND), U7.5 (GND), U8.4 (GND), U8.P (GND), U9.1 (GND), U9.PAD (GND), U10.1 (GND), U10.PAD (GND); also elsewhere on the board
unnamed: R27.2, R29.1, U9.2 (ADJ/SENSE)
unnamed: R28.2, R30.1, U10.2 (ADJ/SENSE)
unnamed: C40.1, R31.2, U5.43 (ADC_VDD)
V1P1: C33.1, C34.1, C35.1, TP12.P$1, U5.23 (DVDD), U5.45 (VREG_VOUT), U5.50 (DVDD)
V3P3: C26.1, C28.1, C36.1, C37.1, C38.1, C39.1, C41.1, C42.1, C43.1, R31.1, TP8.P$1, U5.1 (IOVDD), U5.10 (IOVDD), U5.22 (IOVDD), U5.33 (IOVDD), U5.42 (IOVDD), U5.44 (VREG_VIN), U5.48 (USB_VDD), U5.49 (IOVDD), U8.1 (OUT); also elsewhere on the board
V4P0: C29.1, C31.1, R29.2, TP10.P$1, U9.3 (VOUT); also elsewhere on the board
VBUS: D10.1 (A1), D10.2 (A2); also elsewhere on the board
VIN: D11.1 (A1), D11.2 (A2), F1.2; also elsewhere on the board
VIN_F: C20.P, C21.1, C23.1, C44.1, C45.1, F1.1, U9.4 (VIN), U9.6 (EN), U10.4 (VIN); also elsewhere on the board
VIN_MCU: C22.1, C25.1, D10.3 (C), D11.3 (C), TP7.P$1, U8.5 (/SHDN), U8.8 (IN)
VLED: C30.1, C32.1, C46.1, R30.2, TP11.P$1, U10.3 (VOUT); also elsewhere on the board
VLED_EN: R26.2, U10.6 (EN); also elsewhere on the board
VN1P2: C27.2, TP9.P$1, U7.1 (OUT), U7.2 (NC/ADJ); also elsewhere on the board
VN3P0: C24.2, U7.3 (EN), U7.6 (IN), U7.PAD (IN); also elsewhere on the board

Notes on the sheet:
Voltage Regulators
nominal: 1.18*(24/10+1) = 4.01V
nominal: 1.18*(28/10+1) = 4.48V
